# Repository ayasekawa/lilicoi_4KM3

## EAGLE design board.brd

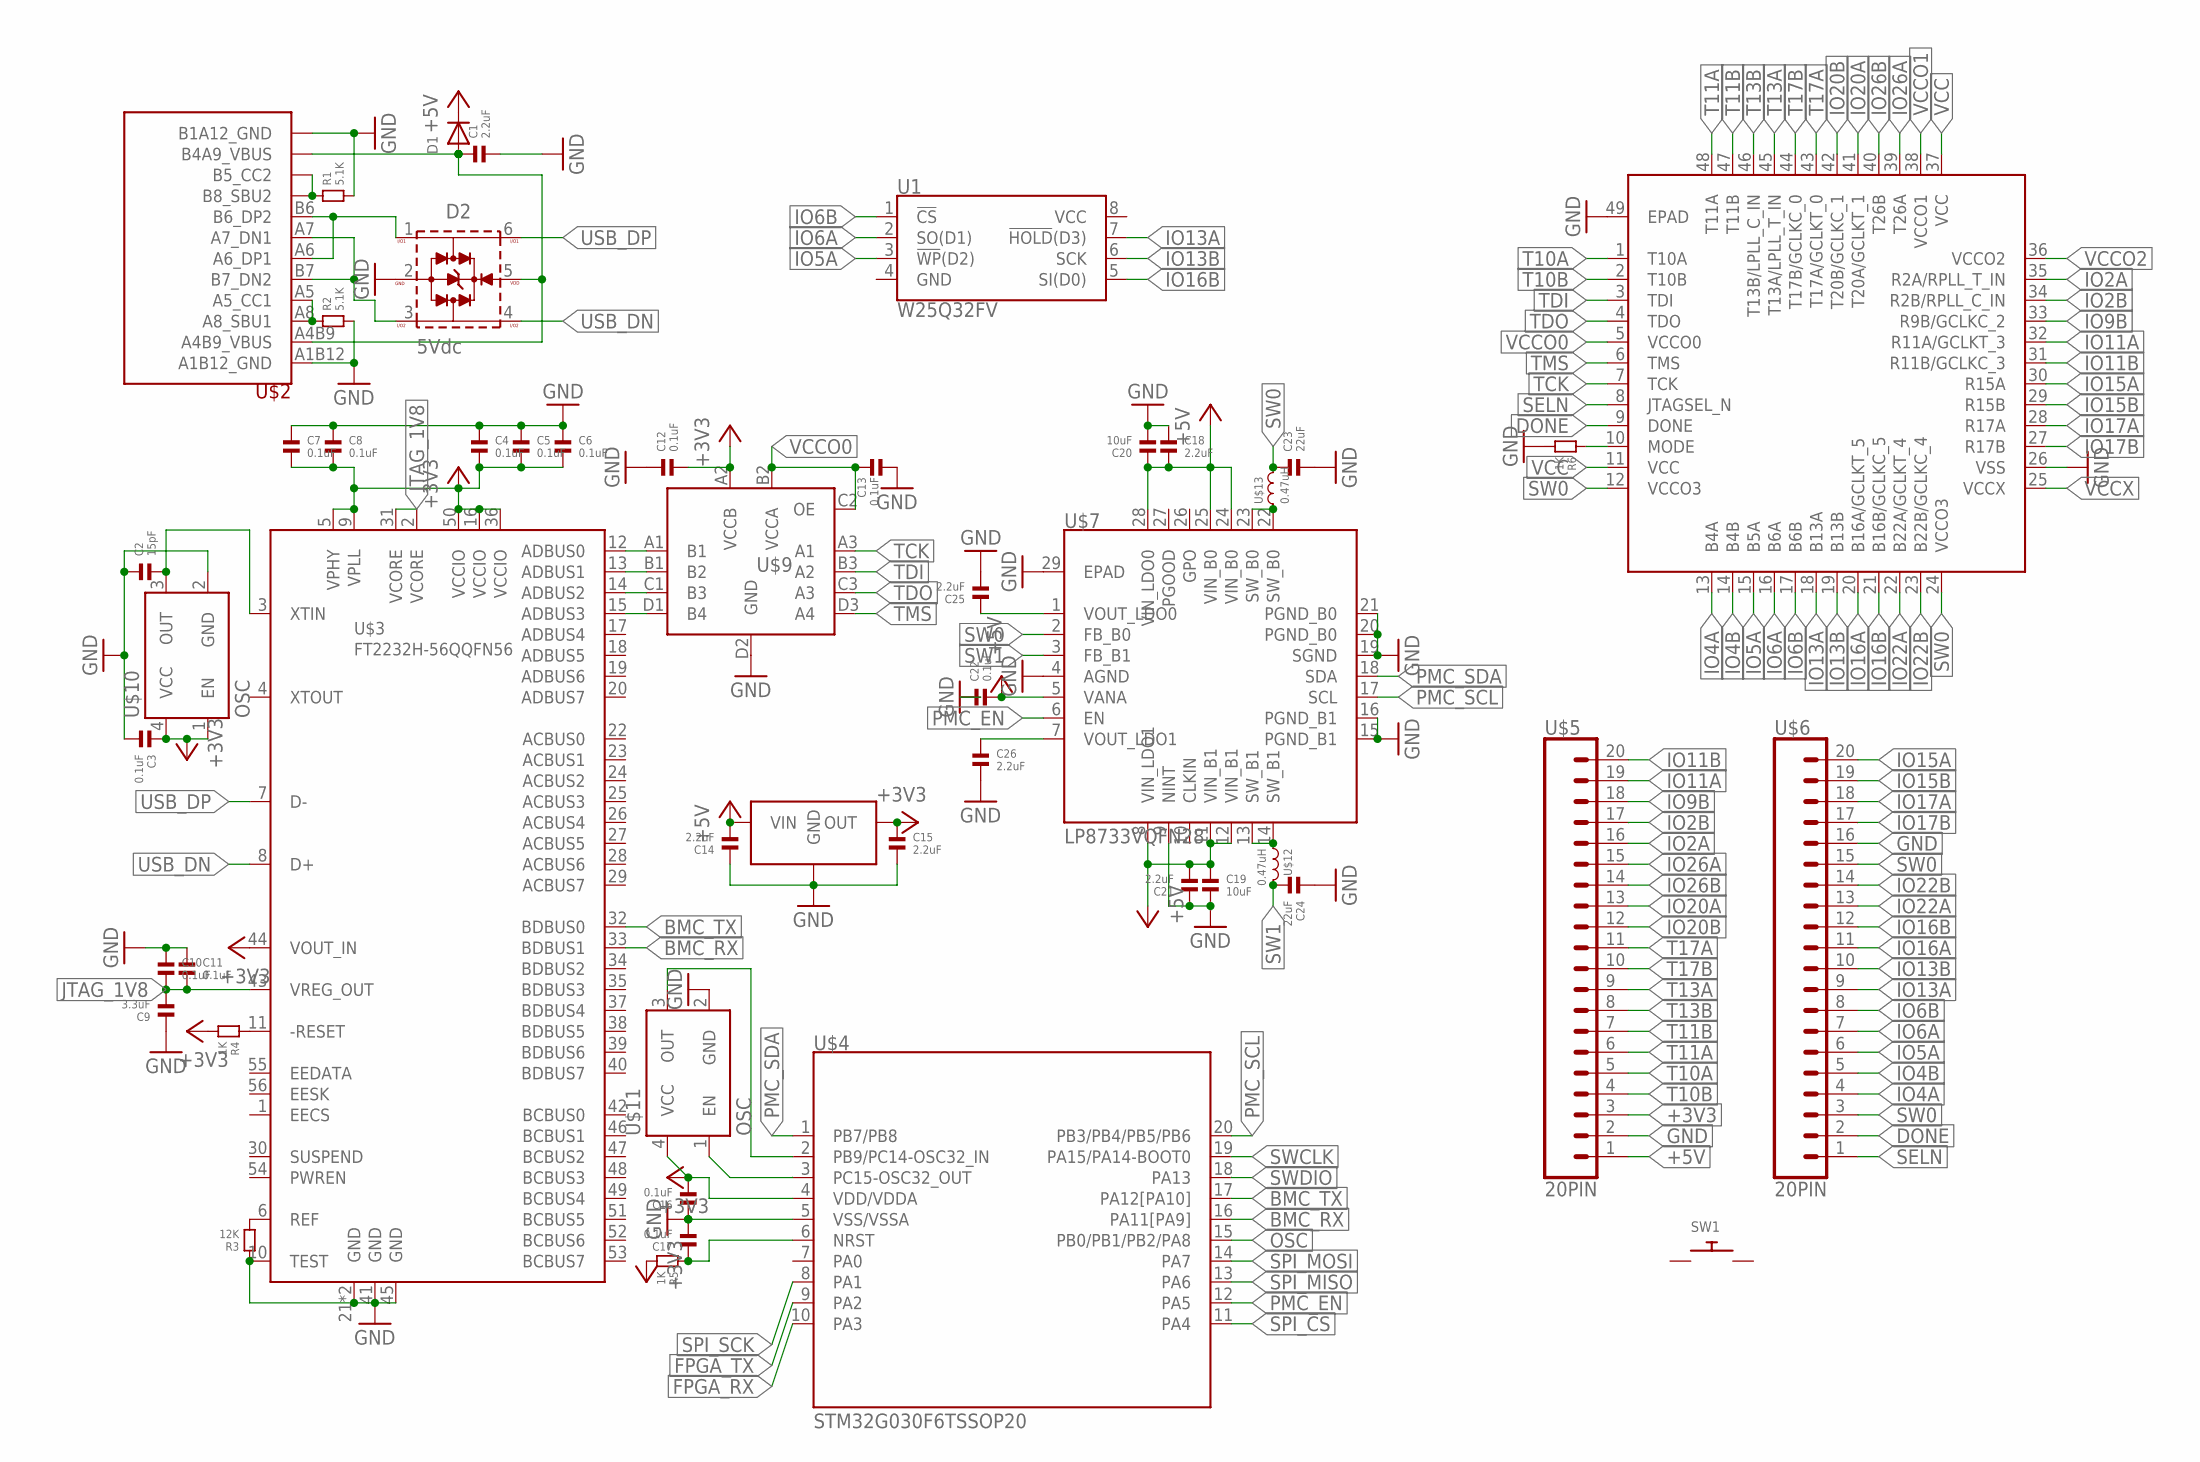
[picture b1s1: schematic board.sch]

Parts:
C1, C14, C15, C18, C21, C25, C26: 2.2uF; 0603_CAP
C2: 15pF; 0402_CAP
C3, C4, C5, C6, C7, C8, C10, C11, C12, C13, C16, C17, C22: 0.1uF; 0402_CAP
C9: 3.3uF; 0603_CAP
C19, C20: 10uF; 0805_CAP
C23, C24: 22uF; 0805_CAP
D1: DIODESOD-323F; SOD-323F
D2: 5Vdc; WE-TVS_SOT23-6L
R1, R2: 5.1K; 0402
R3: 12K; 0402
R4, R5, R6: 1K; 0402
SW1: SWITCH_PUSHBUTTONC&K_KSS; BTN_CK_KSS
U1: W25Q32FV; SOIC-8
U$1: GW1NSR-4CQN48P; QFN40P600X600X80-49T420N
U$2: TYPEC; TYPE-C-31-M-12
U$3: FT2232H-56QQFN56; QFN50P800X800X90-57T595N
U$4: STM32G030F6TSSOP20; SOP65P640X120-20N
U$5, U$6: 20PIN; HDRV20W64P254_1X20_5080X254X838B
U$7: LP8733VQFN28; QFN50P500X500X100-29T340N
U$8: XC6206; SOT95P280X125-3
U$9: TXS0104EYZTR; BGA12C50P3X4_186X136X62N
U$10, U$11: OSC; OSCCC200X160X85N
U$12, U$13: 0.47uH; INDM2621X120

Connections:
+3V3: C3.1, C4.2, C5.2, C6.2, C7.2, C8.2, C12.2, C15.1, C16.2, R4.2, R5.2, U$3.5 (VPHY), U$3.9 (VPLL), U$3.16 (VCCIO), U$3.36 (VCCIO), U$3.44 (VOUT_IN), U$3.50 (VCCIO), U$4.4 (VDD/VDDA), U$5.3, U$8.2 (OUT), U$9.A2 (VCCB), U$10.1 (EN), U$10.4 (VCC), U$11.4 (VCC)
+5V: C14.2, C18.2, C19.1, C20.1, C21.2, C22.2, D1.C, U$5.1, U$7.5 (VANA), U$7.8 (VIN_LDO1), U$7.11 (VIN_B1), U$7.12 (VIN_B1), U$7.24 (VIN_B0), U$7.25 (VIN_B0), U$7.28 (VIN_LDO0), U$8.3 (VIN)
BMC_RX: U$3.33 (BDBUS1), U$4.16 (PA11[PA9])
BMC_TX: U$3.32 (BDBUS0), U$4.17 (PA12[PA10])
DONE: U$1.9 (DONE), U$6.2
FB0: U$7.22 (SW_B0), U$7.23 (SW_B0), U$13.1
FB1: U$7.13 (SW_B1), U$7.14 (SW_B1), U$12.1
FPGA_RX: U$4.10 (PA3)
FPGA_TX: U$4.9 (PA2)
GND: C1.2, C2.1, C3.2, C4.1, C5.1, C6.1, C7.1, C8.1, C9.1, C10.1, C11.1, C12.1, C13.2, C14.1, C15.2, C16.1, C17.2, C18.1, C19.2, C20.2, C21.1, C22.1, C23.2, C24.1, C25.2, C26.2, D2.2 (GND), R1.2, R2.2, R3.1, R6.2, U$1.26 (VSS), U$1.49 (EPAD), U$2.A1B12 (A1B12_GND), U$2.B1A12 (B1A12_GND), U$3.10 (TEST), U$3.21 (GND), U$3.41 (GND), U$3.45 (GND), U$3.57 (GND), U$4.5 (VSS/VSSA), U$5.2, U$6.16, U$7.4 (AGND), U$7.9 (NINT), U$7.15 (PGND_B1), U$7.16 (PGND_B1), U$7.19 (SGND), U$7.20 (PGND_B0), U$7.21 (PGND_B0), U$7.29 (EPAD), U$8.1 (GND), U$9.D2 (GND), U$10.2 (GND), U$11.2 (GND)
IO2A: U$1.35 (R2A/RPLL_T_IN), U$5.16
IO2B: U$1.34 (R2B/RPLL_C_IN), U$5.17
IO4A: U$1.13 (B4A), U$6.4
IO4B: U$1.14 (B4B), U$6.5
IO5A: U1.3 (!WP!(D2)), U$1.15 (B5A), U$6.6
IO6A: U1.2 (SO(D1)), U$1.16 (B6A), U$6.7
IO6B: U1.1 (!CS!), U$1.17 (B6B), U$6.8
IO9B: U$1.33 (R9B/GCLKC_2), U$5.18
IO11A: U$1.32 (R11A/GCLKT_3), U$5.19
IO11B: U$1.31 (R11B/GCLKC_3), U$5.20
IO13A: U1.7 (!HOLD!(D3)), U$1.18 (B13A), U$6.9
IO13B: U1.6 (SCK), U$1.19 (B13B), U$6.10
IO15A: U$1.30 (R15A), U$6.20
IO15B: U$1.29 (R15B), U$6.19
IO16A: U$1.20 (B16A/GCLKT_5), U$6.11
IO16B: U1.5 (SI(D0)), U$1.21 (B16B/GCLKC_5), U$6.12
IO17A: U$1.28 (R17A), U$6.18
IO17B: U$1.27 (R17B), U$6.17
IO20A: U$1.41 (T20A/GCLKT_1), U$5.13
IO20B: U$1.42 (T20B/GCLKC_1), U$5.12
IO22A: U$1.22 (B22A/GCLKT_4), U$6.13
IO22B: U$1.23 (B22B/GCLKC_4), U$6.14
IO26A: U$1.39 (T26A), U$5.15
IO26B: U$1.40 (T26B), U$5.14
JTAG_1V8: C9.2, C10.2, C11.2, U$3.2 (VCORE), U$3.31 (VCORE), U$3.43 (VREG_OUT)
unnamed: C2.2, U$3.3 (XTIN), U$10.3 (OUT)
unnamed: U$3.12 (ADBUS0), U$9.A1 (B1)
unnamed: U$3.13 (ADBUS1), U$9.B1 (B2)
unnamed: U$3.14 (ADBUS2), U$9.C1 (B3)
unnamed: U$3.15 (ADBUS3), U$9.D1 (B4)
unnamed: D2.1 (I/O1), U$2.A6 (A6_DP1), U$2.B6 (B6_DP2)
unnamed: D2.3 (I/O2), U$2.A7 (A7_DN1), U$2.B7 (B7_DN2)
unnamed: C1.1, D1.A, D2.5 (VDD), U$2.A4B9 (A4B9_VBUS), U$2.B4A9 (B4A9_VBUS)
unnamed: R2.1, U$2.A5 (A5_CC1), U$2.A8 (A8_SBU1)
unnamed: R1.1, U$2.B5 (B5_CC2), U$2.B8 (B8_SBU2)
unnamed: R3.2, U$3.6 (REF)
unnamed: R4.1, U$3.11 (-RESET)
unnamed: C17.1, R5.1, U$4.6 (NRST)
unnamed: R6.1, U$1.10 (MODE)
unnamed: C25.1, U$7.1 (VOUT_LDO0)
unnamed: U$4.2 (PB9/PC14-OSC32_IN), U$11.3 (OUT)
unnamed: U$4.3 (PC15-OSC32_OUT), U$11.1 (EN)
unnamed: C26.1, U$7.7 (VOUT_LDO1)
OSC: U$4.15 (PB0/PB1/PB2/PA8)
PMC_EN: U$4.12 (PA5), U$7.6 (EN)
PMC_SCL: U$4.20 (PB3/PB4/PB5/PB6), U$7.17 (SCL)
PMC_SDA: U$4.1 (PB7/PB8), U$7.18 (SDA)
SELN: U$1.8 (JTAGSEL_N), U$6.1
SPI_CS: U$4.11 (PA4)
SPI_MISO: U$4.13 (PA6)
SPI_MOSI: U$4.14 (PA7)
SPI_SCK: U$4.8 (PA1)
SW0: C23.1, U$1.12 (VCCO3), U$1.24 (VCCO3), U$6.3, U$6.15, U$7.2 (FB_B0), U$13.2
SW1: C24.2, U$7.3 (FB_B1), U$12.2
SWCLK: U$4.19 (PA15/PA14-BOOT0)
SWDIO: U$4.18 (PA13)
T10A: U$1.1 (T10A), U$5.5
T10B: U$1.2 (T10B), U$5.4
T11A: U$1.48 (T11A), U$5.6
T11B: U$1.47 (T11B), U$5.7
T13A: U$1.45 (T13A/LPLL_T_IN), U$5.9
T13B: U$1.46 (T13B/LPLL_C_IN), U$5.8
T17A: U$1.43 (T17A/GCLKT_0), U$5.11
T17B: U$1.44 (T17B/GCLKC_0), U$5.10
TCK: U$1.7 (TCK), U$9.A3 (A1)
TDI: U$1.3 (TDI), U$9.B3 (A2)
TDO: U$1.4 (TDO), U$9.C3 (A3)
TMS: U$1.6 (TMS), U$9.D3 (A4)
USB_DN: D2.4 (I/O4), U$3.8 (D+)
USB_DP: D2.6 (I/O3), U$3.7 (D-)
VCC: U$1.11 (VCC), U$1.37 (VCC)
VCCO0: C13.1, U$1.5 (VCCO0), U$9.B2 (VCCA), U$9.C2 (OE)
VCCO1: U$1.38 (VCCO1)
VCCO2: U$1.36 (VCCO2)
VCCX: U$1.25 (VCCX)

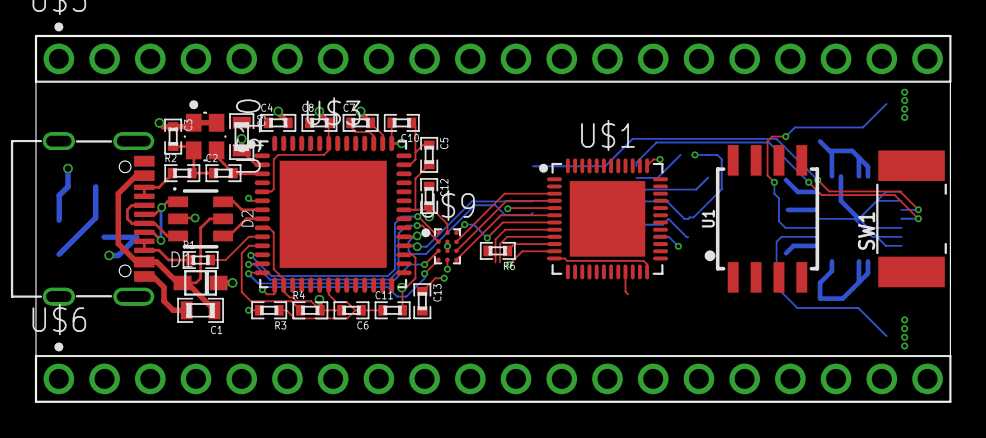
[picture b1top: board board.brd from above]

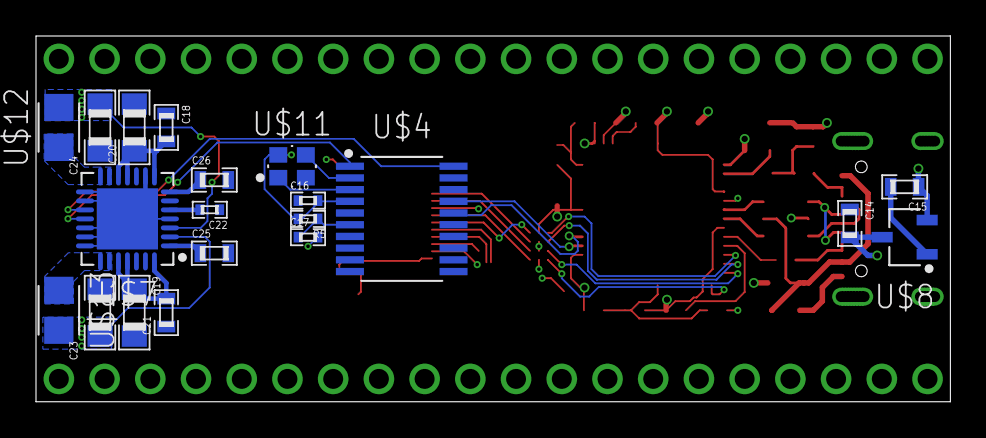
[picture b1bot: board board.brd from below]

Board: 4 copper layers, 50.8 x 20.3 mm, 49 parts (20 on the bottom side), 73 nets.

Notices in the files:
parts and their libraries:
Wurth_EMC Components_WE-TVS: Copyright: Würth Elektronik
